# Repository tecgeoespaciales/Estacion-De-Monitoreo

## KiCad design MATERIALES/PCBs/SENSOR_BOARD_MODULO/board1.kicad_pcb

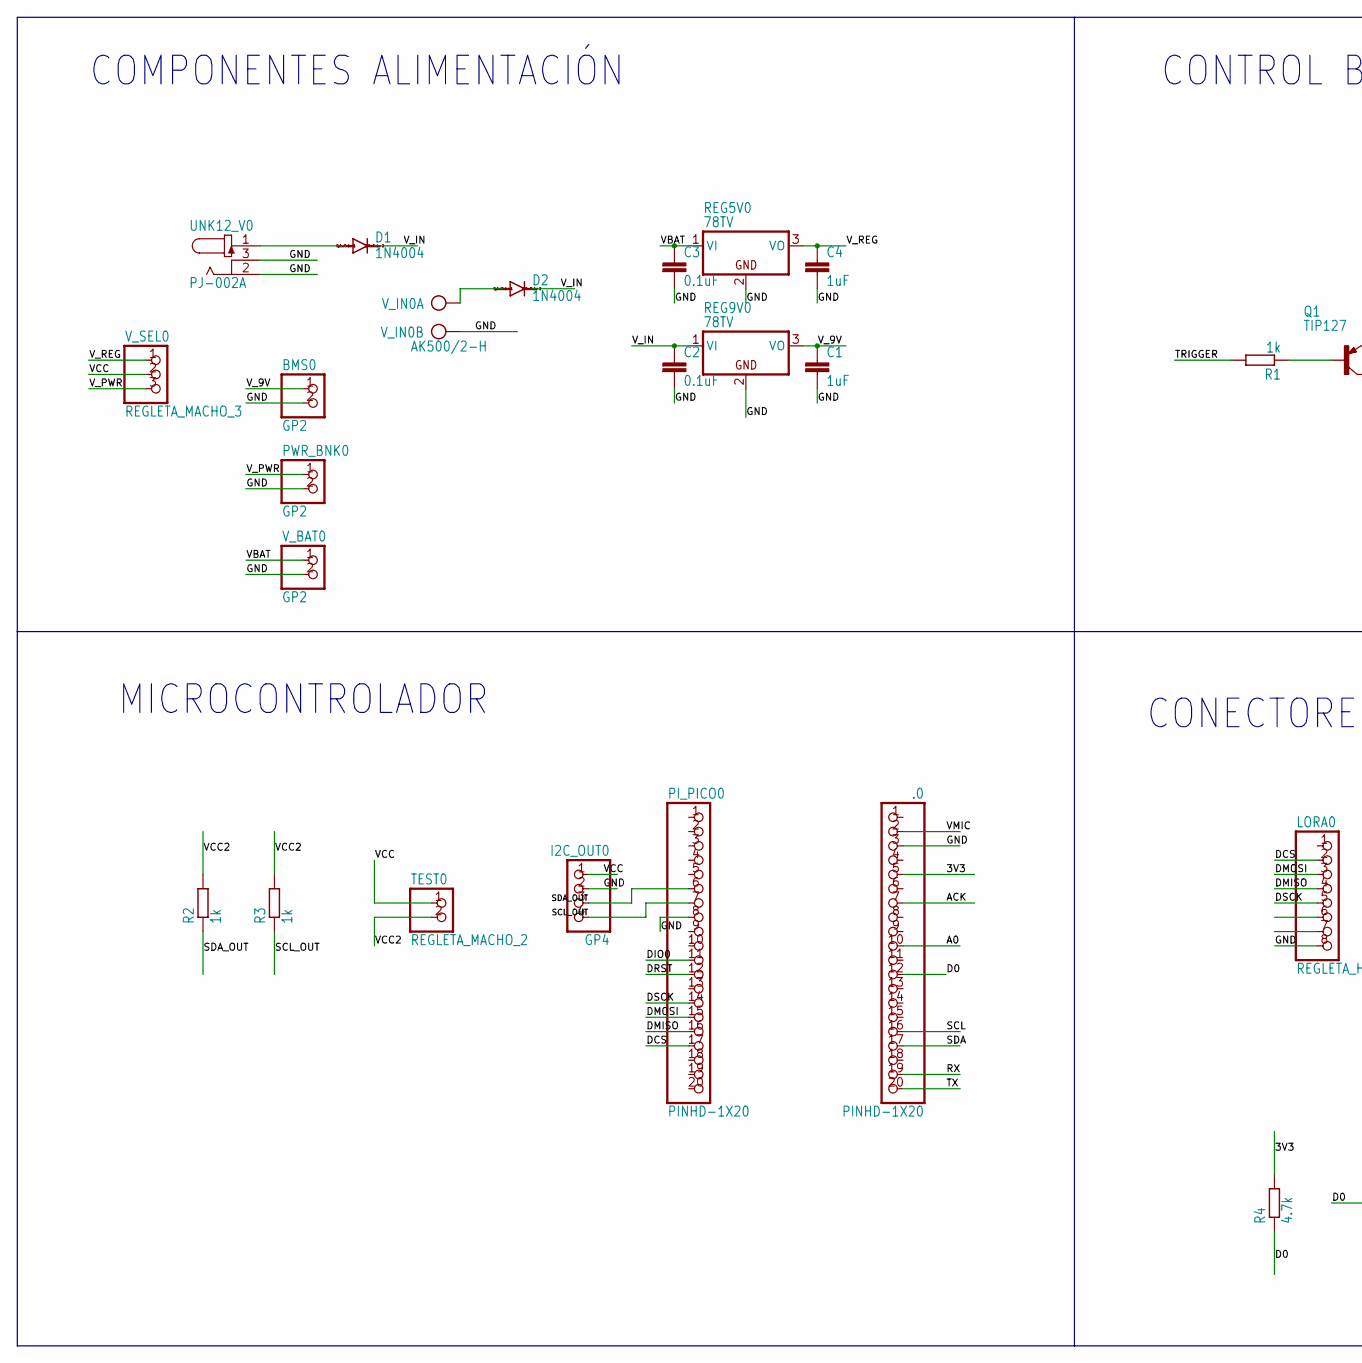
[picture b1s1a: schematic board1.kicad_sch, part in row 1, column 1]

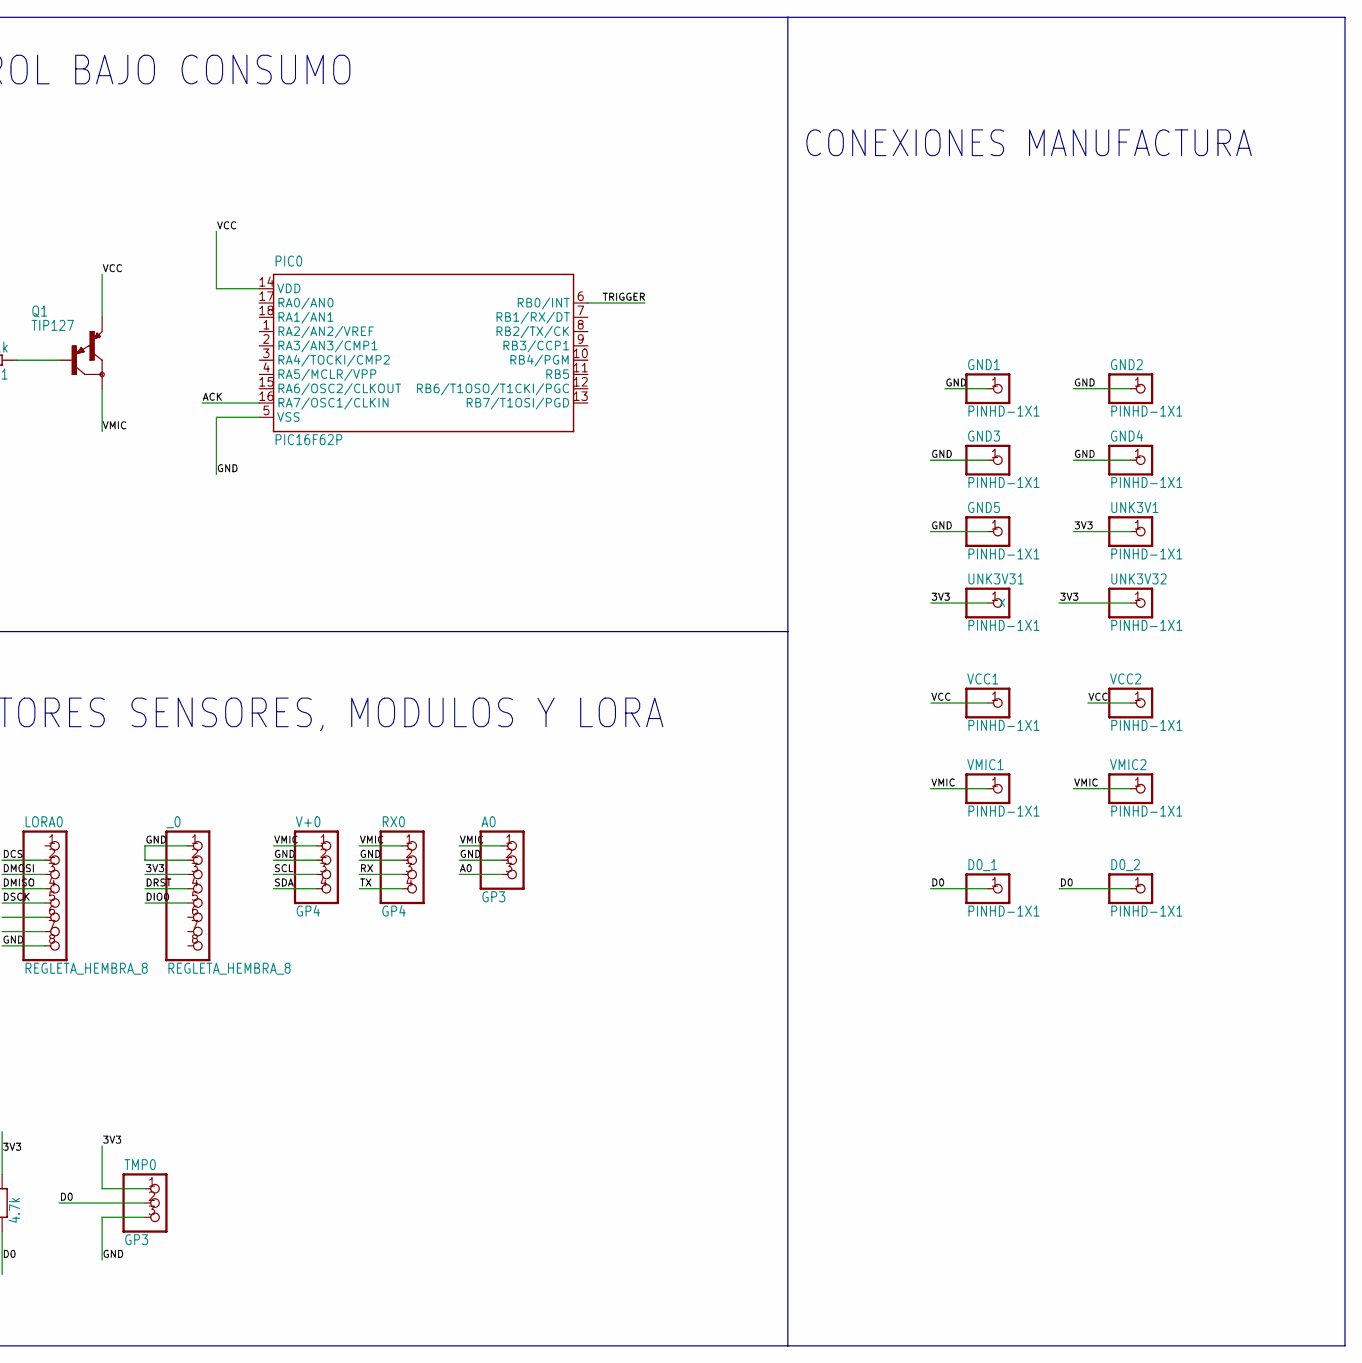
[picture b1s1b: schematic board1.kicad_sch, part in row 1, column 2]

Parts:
.0: PINHD-1X20; 1X20
A0: GP3; 1X03
BMS0: GP2; 1X02
C1, C4: 1uF; C025-024X044
C2, C3: 0.1uF; C025-024X044
D0_1, D0_2: PINHD-1X1; 1X01
D1, D2: 1N4004; DO41-10
GND1, GND2, GND3, GND4, GND5: PINHD-1X1; 1X01
I2C_OUT0: GP4; 1X04
LORA0: REGLETA_HEMBRA_8; 1X08
PIC0: PIC16F62P; DIL18
PI_PICO0: PINHD-1X20; 1X20
PWR_BNK0: GP2; 1X02
Q1: TIP127; TO220
R1, R2, R3: 1k; 0204_7
R4: 4.7k; 0204_7
REG5V0, REG9V0: 78TV; TO220V
RX0: GP4; 1X04
TEST0: REGLETA_MACHO_2; 1X02
TMP0: GP3; 1X03
UNK3V1, UNK3V31, UNK3V32: PINHD-1X1; 1X01
UNK12_V0: PJ-002A; CUI_PJ-002A
V+0: GP4; 1X04
VCC1, VCC2: PINHD-1X1; 1X01
VMIC1, VMIC2: PINHD-1X1; 1X01
V_BAT0: GP2; 1X02
V_IN0: AK500/2-H; AK500_2-H
V_SEL0: REGLETA_MACHO_3; 1X03
_0: REGLETA_HEMBRA_8; 1X08

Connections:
3V3: .0.5, R4.2, TMP0.1, UNK3V1.1, UNK3V31.1, UNK3V32.1, _0.3
A0: .0.10, A0.3
ACK: .0.7, PIC0.16 (RA7/OSC1/CLKIN)
D0: .0.12, D0_1.1, D0_2.1, R4.1, TMP0.2
DCS: LORA0.2, PI_PICO0.17
DIO0: PI_PICO0.11, _0.5
DMISO: LORA0.4, PI_PICO0.16
DMOSI: LORA0.3, PI_PICO0.15
DRST: PI_PICO0.12, _0.4
DSCK: LORA0.5, PI_PICO0.14
GND: .0.3, A0.2, BMS0.2, C1.2, C2.2, C3.2, C4.2, GND1.1, GND2.1, GND3.1, GND4.1, GND5.1, I2C_OUT0.2, LORA0.8, PIC0.5 (VSS), PI_PICO0.8, PWR_BNK0.2, REG5V0.2 (GND), REG9V0.2 (GND), RX0.2, TMP0.3, UNK12_V0.2, UNK12_V0.3, V+0.2, V_BAT0.2, V_IN0.2, _0.1, _0.2
unnamed: D1.A, UNK12_V0.1
unnamed: Q1.1 (B), R1.1
unnamed: D2.A, V_IN0.1
RX: .0.19, RX0.3
SCL: .0.16, V+0.3
SCL_OUT: I2C_OUT0.4, PI_PICO0.7, R3.1
SDA: .0.17, V+0.4
SDA_OUT: I2C_OUT0.3, PI_PICO0.6, R2.1
TRIGGER: PIC0.6 (RB0/INT), R1.2
TX: .0.20, RX0.4
VBAT: C3.1, REG5V0.1 (VI), V_BAT0.1
VCC: I2C_OUT0.1, PIC0.14 (VDD), Q1.3 (E), TEST0.1, VCC1.1, VCC2.1, V_SEL0.2
VCC2: R2.2, R3.2, TEST0.2
VMIC: .0.2, A0.1, Q1.2 (C), RX0.1, V+0.1, VMIC1.1, VMIC2.1
V_9V: BMS0.1, C1.1, REG9V0.3 (VO)
V_IN: C2.1, D1.C, D2.C, REG9V0.1 (VI)
V_PWR: PWR_BNK0.1, V_SEL0.3
V_REG: C4.1, REG5V0.3 (VO), V_SEL0.1

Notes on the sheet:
CONECTORES SENSORES, MODULOS Y LORA
CONEXIONES MANUFACTURA
CONTROL BAJO CONSUMO
MICROCONTROLADOR
COMPONENTES ALIMENTACIÓN

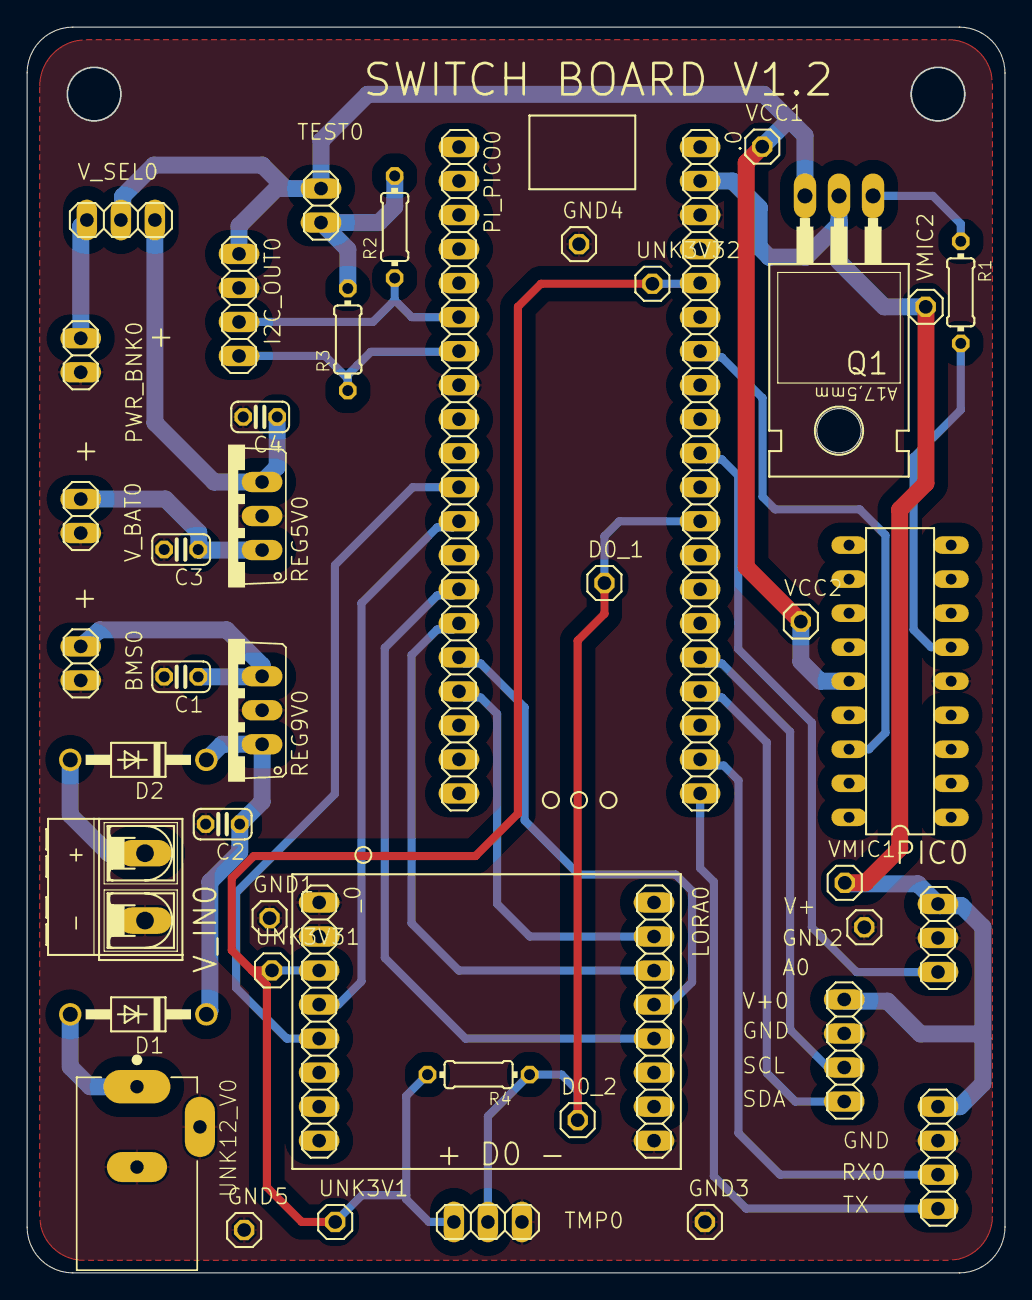
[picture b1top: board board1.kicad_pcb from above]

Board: 2 copper layers, 72.9 x 92.9 mm, 44 parts (0 on the bottom side), 29 nets.

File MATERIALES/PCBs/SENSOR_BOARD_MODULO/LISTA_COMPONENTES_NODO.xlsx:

Reference | Qty | Value | DNP | Exclude from BOM | Exclude from Board | Footprint | Datasheet
PI_PICO | 1 | PI_PICO |  |  |  | board1:PI_PICO
.0,PI_PICO0 | 2 | REGLETA_HEMBRA_20 |  |  |  | board1:1X20
A0,TMP0 | 2 | GP3 |  |  |  | board1:1X03
BMS0,PWR_BNK0,V_BAT0 | 3 | GP2 |  |  |  | board1:1X02
C1,C4 | 2 | 1uF |  |  |  | board1:C025-024X044
C2,C3 | 2 | 0.1uF |  |  |  | board1:C025-024X044
D0_1,D0_2,GND1,GND2,GND3,GND4,GND5,UNK3V1,UNK3V31,UNK3V32,VCC1,VCC2,VMIC1,VMIC2 | 14 | PINHD-1X1 |  |  |  | board1:1X01
D1,D2 | 2 | 1N4004 |  |  |  | board1:DO41-10
I2C_OUT0,RX0,V+0 | 3 | GP4 |  |  |  | board1:1X04
LORA0,_0 | 2 | REGLETA_HEMBRA_8 |  |  |  | board1:1X08
PIC0 | 1 | PIC16F62P |  |  |  | board1:DIL18
Q1 | 1 | TIP127 |  |  |  | board1:TO220
R1,R2,R3 | 3 | 1k |  |  |  | board1:0204_7
R4 | 1 | 4.7k |  |  |  | board1:0204_7
REG5V0,REG9V0 | 2 | 78TV |  |  |  | board1:TO220V
TEST0 | 1 | REGLETA_MACHO_2 |  |  |  | board1:1X02
UNK12_V0 | 1 | PJ-002A |  |  |  | board1:CUI_PJ-002A
V_IN0 | 1 | AK500/2-H |  |  |  | board1:AK500_2-H
V_SEL0 | 1 | REGLETA_MACHO_3 |  |  |  | board1:1X03

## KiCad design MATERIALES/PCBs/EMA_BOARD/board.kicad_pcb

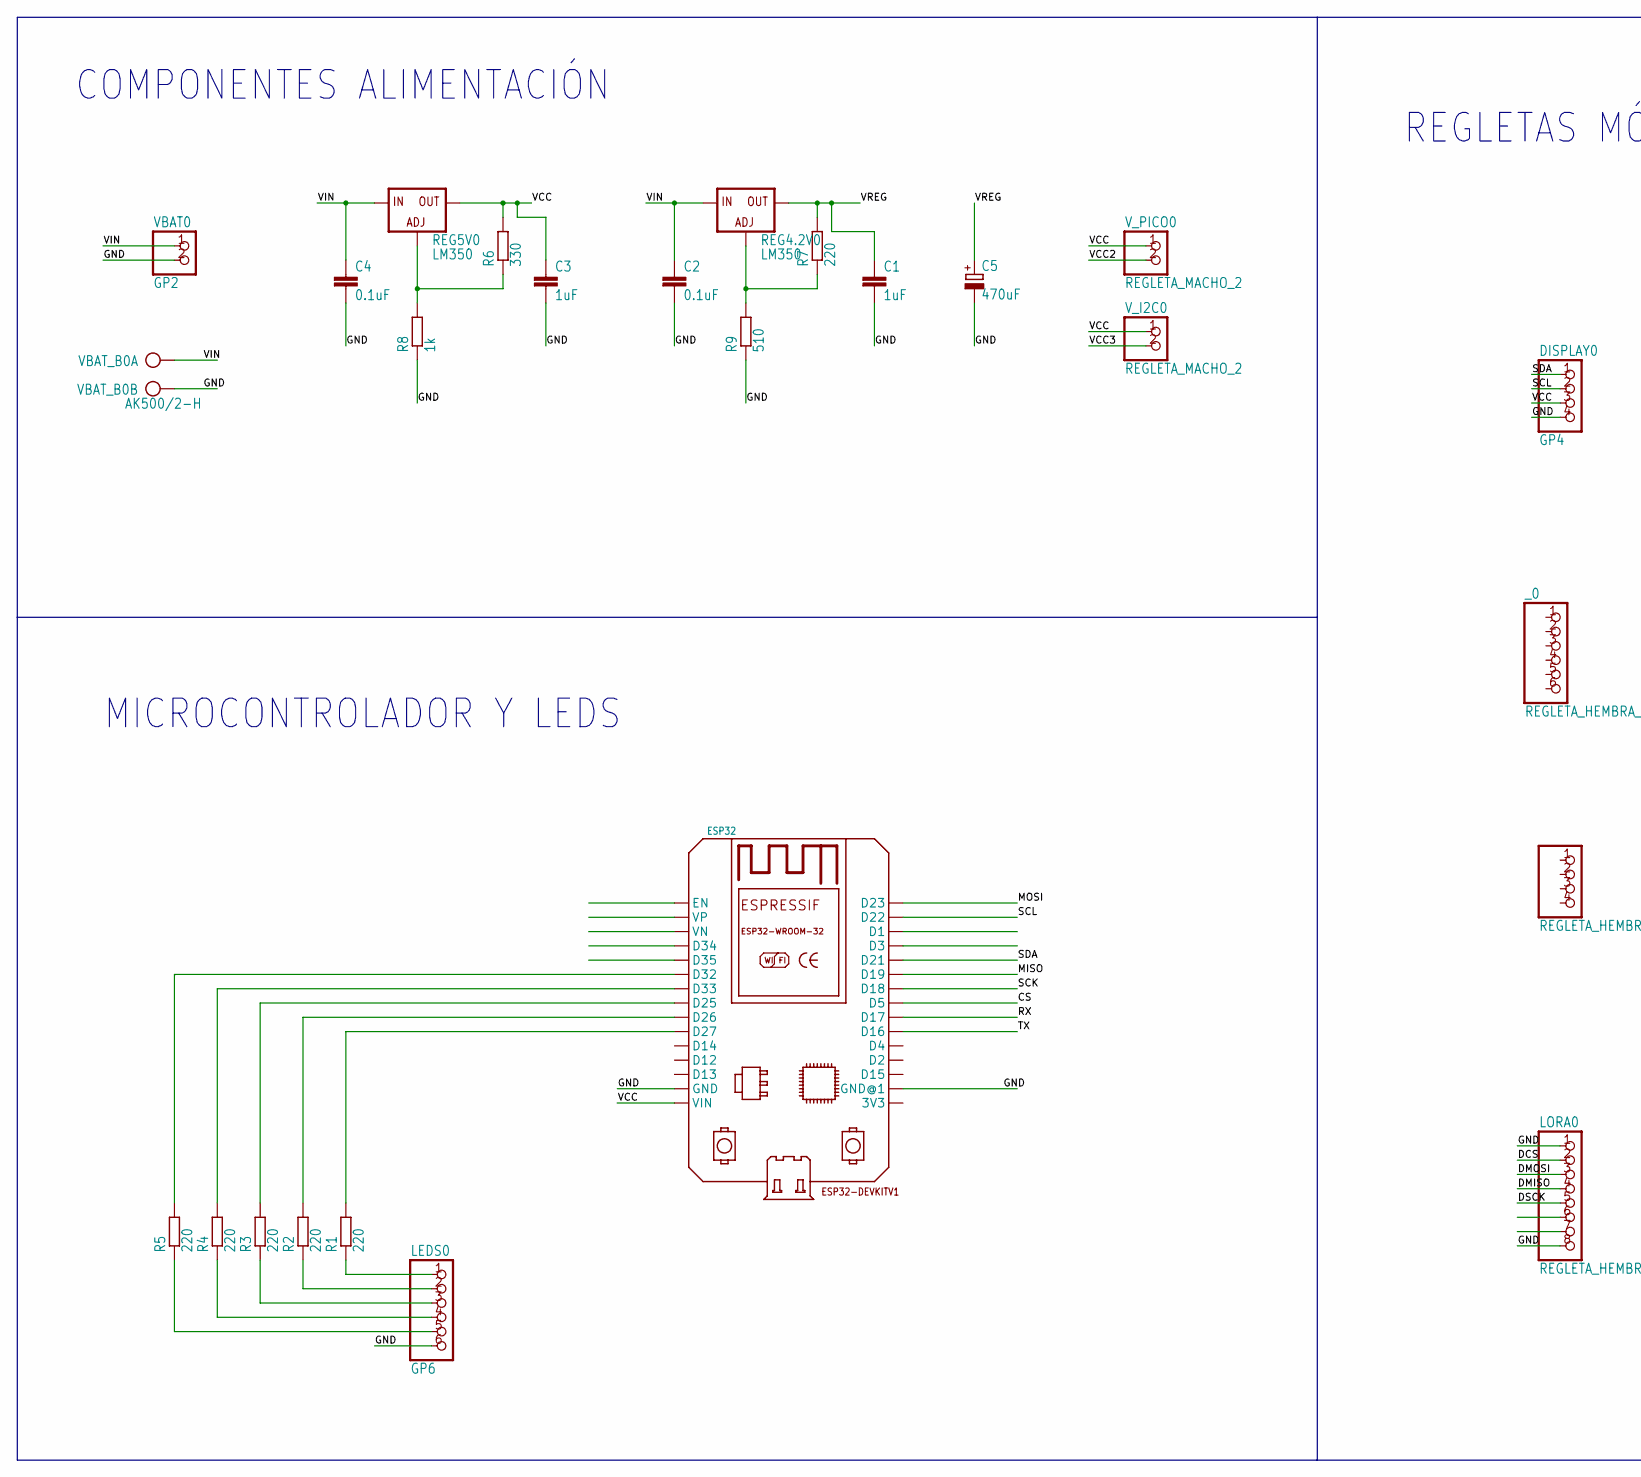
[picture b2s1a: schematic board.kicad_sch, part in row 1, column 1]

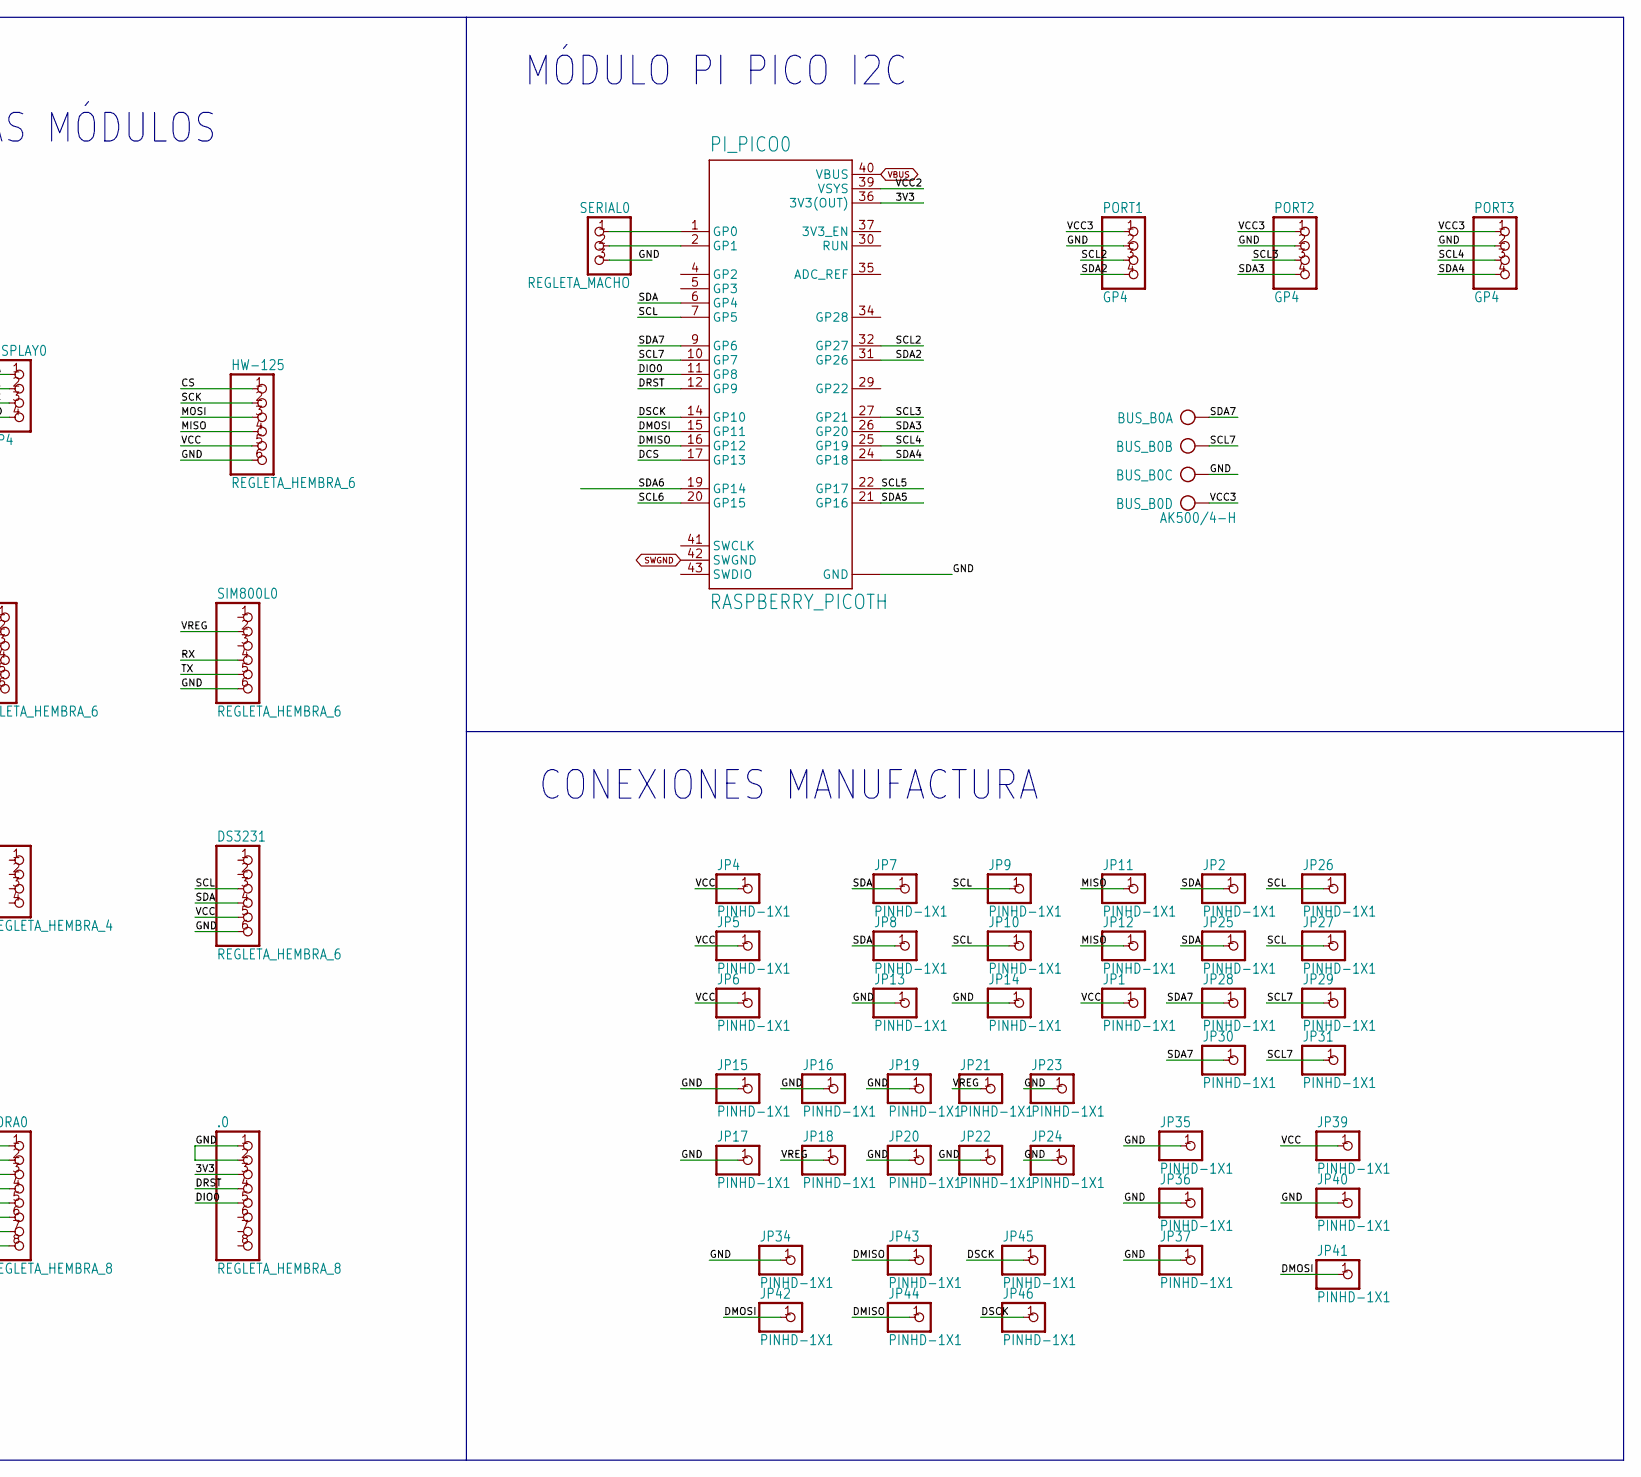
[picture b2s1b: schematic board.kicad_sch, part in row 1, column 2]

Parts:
.0: REGLETA_HEMBRA_8; 1X08
BUS_B0: AK500/4-H; AK500_4-H
C1, C3: 1uF; C2.5-2
C2, C4: 0.1uF; C2.5-2
C5: 470uF; E3,5-8
DISPLAY0: GP4; 1X04
DS3231: REGLETA_HEMBRA_6; 1X06
ESP32: ESP32DEVKITV1; ESP32-DEVKITV1
HW-125: REGLETA_HEMBRA_6; 1X06
JP1, JP2, JP4, JP5, JP6, JP7, JP8, JP9, JP10, JP11, JP12, JP13, JP14, JP15, JP16, JP17, JP18, JP19, JP20, JP21, JP22, JP23, JP24, JP25, JP26, JP27, JP28, JP29, JP30, JP31, JP34, JP35, JP36, JP37, JP39, JP40, JP41, JP42, JP43, JP44, JP45, JP46: PINHD-1X1; 1X01
LEDS0: GP6; 1X06
LORA0: REGLETA_HEMBRA_8; 1X08
PI_PICO0: RASPBERRY_PICOTH; PICO-PKG-TH
PORT1, PORT2, PORT3: GP4; 1X04
R1, R2, R3, R4, R5, R7: 220; 0204_7
R6: 330; 0204_7
R8: 1k; 0204_7
R9: 510; 0204_7
REG4.2V0, REG5V0: LM350; 317TS
SERIAL0: REGLETA_MACHO; 1X03
SIM800L0: REGLETA_HEMBRA_6; 1X06
VBAT0: GP2; 1X02
VBAT_B0: AK500/2-H; AK500_2-H
V_I2C0: REGLETA_MACHO_2; 1X02
V_PICO0: REGLETA_MACHO_2; 1X02
_: REGLETA_HEMBRA_4; 1X04
_0: REGLETA_HEMBRA_6; 1X06

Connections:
3V3: .0.3, PI_PICO0.36 (3V3(OUT))
CS: ESP32.D5, HW-125.1
DCS: LORA0.2, PI_PICO0.17 (GP13)
DIO0: .0.5, PI_PICO0.11 (GP8)
DMISO: JP43.1, JP44.1, LORA0.4, PI_PICO0.16 (GP12)
DMOSI: JP41.1, JP42.1, LORA0.3, PI_PICO0.15 (GP11)
DRST: .0.4, PI_PICO0.12 (GP9)
DSCK: JP45.1, JP46.1, LORA0.5, PI_PICO0.14 (GP10)
GND: .0.1, .0.2, BUS_B0.3, C1.2, C2.2, C3.2, C4.2, C5.-, DISPLAY0.4, DS3231.6, ESP32.GND, ESP32.GND@1, HW-125.6, JP13.1, JP14.1, JP15.1, JP16.1, JP17.1, JP19.1, JP20.1, JP22.1, JP23.1, JP24.1, JP34.1, JP35.1, JP36.1, JP37.1, JP40.1, LEDS0.6, LORA0.1, LORA0.8, PI_PICO0.3 (GND), PI_PICO0.8 (GND), PI_PICO0.13 (GND), PI_PICO0.18 (GND), PI_PICO0.23 (GND), PI_PICO0.28 (GND), PI_PICO0.33 (GND), PI_PICO0.38 (GND), PORT1.2, PORT2.2, PORT3.2, R8.1, R9.1, SERIAL0.3, SIM800L0.6, VBAT0.2, VBAT_B0.2
MISO: ESP32.D19, HW-125.4, JP11.1, JP12.1
MOSI: ESP32.D23, HW-125.3
unnamed: ESP32.D32, R5.2
unnamed: ESP32.D33, R4.2
unnamed: ESP32.D25, R3.2
unnamed: ESP32.D26, R2.2
unnamed: ESP32.D27, R1.2
unnamed: LEDS0.1, R1.1
unnamed: PI_PICO0.1 (GP0), SERIAL0.1
unnamed: LEDS0.2, R2.1
unnamed: LEDS0.3, R3.1
unnamed: LEDS0.4, R4.1
unnamed: LEDS0.5, R5.1
unnamed: PI_PICO0.2 (GP1), SERIAL0.2
unnamed: R6.1, R8.2, REG5V0.1 (ADJ)
unnamed: R7.1, R9.2, REG4.2V0.1 (ADJ)
RX: ESP32.D17, SIM800L0.4
SCK: ESP32.D18, HW-125.2
SCL: DISPLAY0.2, DS3231.3, ESP32.D22, JP9.1, JP10.1, JP26.1, JP27.1, PI_PICO0.7 (GP5)
SCL2: PI_PICO0.32 (GP27), PORT1.3
SCL3: PI_PICO0.27 (GP21), PORT2.3
SCL4: PI_PICO0.25 (GP19), PORT3.3
SCL5: PI_PICO0.22 (GP17)
SCL6: PI_PICO0.20 (GP15)
SCL7: BUS_B0.2, JP29.1, JP31.1, PI_PICO0.10 (GP7)
SDA: DISPLAY0.1, DS3231.4, ESP32.D21, JP2.1, JP7.1, JP8.1, JP25.1, PI_PICO0.6 (GP4)
SDA2: PI_PICO0.31 (GP26), PORT1.4
SDA3: PI_PICO0.26 (GP20), PORT2.4
SDA4: PI_PICO0.24 (GP18), PORT3.4
SDA5: PI_PICO0.21 (GP16)
SDA6: PI_PICO0.19 (GP14)
SDA7: BUS_B0.1, JP28.1, JP30.1, PI_PICO0.9 (GP6)
SWGND: PI_PICO0.42 (SWGND)
TX: ESP32.D16, SIM800L0.5
VBUS: PI_PICO0.40 (VBUS)
VCC: C3.1, DISPLAY0.3, DS3231.5, ESP32.VIN, HW-125.5, JP1.1, JP4.1, JP5.1, JP6.1, JP39.1, R6.2, REG5V0.2 (OUT), V_I2C0.1, V_PICO0.1
VCC2: PI_PICO0.39 (VSYS), V_PICO0.2
VCC3: BUS_B0.4, PORT1.1, PORT2.1, PORT3.1, V_I2C0.2
VIN: C2.1, C4.1, REG4.2V0.3 (IN), REG5V0.3 (IN), VBAT0.1, VBAT_B0.1
VREG: C1.1, C5.+, JP18.1, JP21.1, R7.2, REG4.2V0.2 (OUT), SIM800L0.2

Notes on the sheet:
REGLETAS MÓDULOS
MÓDULO PI PICO I2C
COMPONENTES ALIMENTACIÓN
MICROCONTROLADOR Y LEDS
CONEXIONES MANUFACTURA

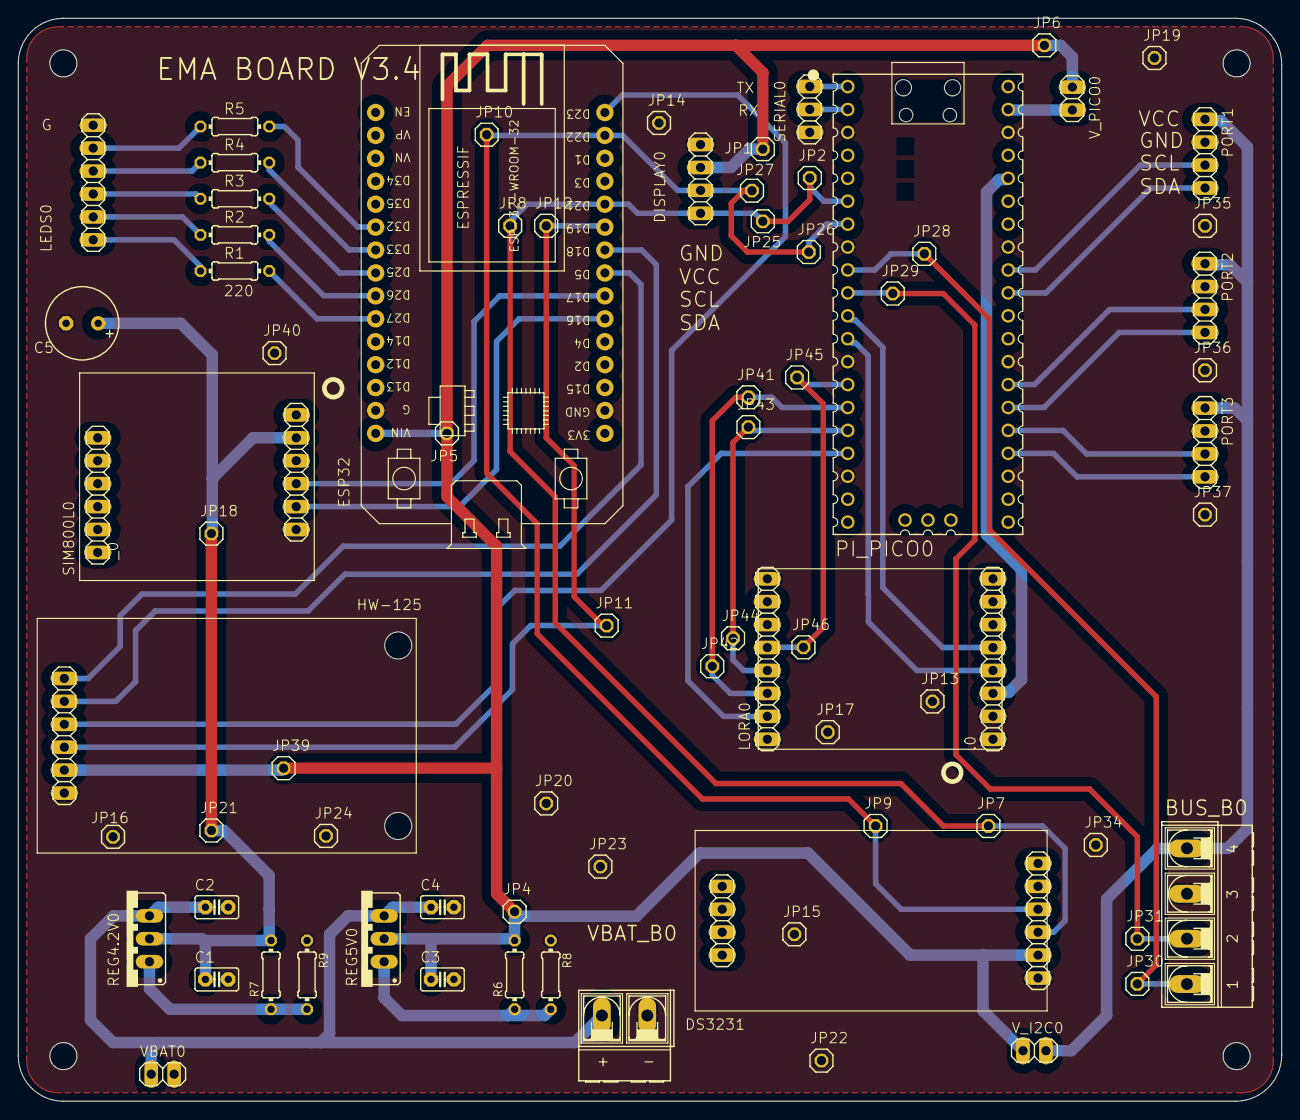
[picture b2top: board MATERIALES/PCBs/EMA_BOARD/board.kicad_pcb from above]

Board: 2 copper layers, 139.9 x 119.9 mm, 78 parts (0 on the bottom side), 43 nets.

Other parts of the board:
JP3: 1X04_325

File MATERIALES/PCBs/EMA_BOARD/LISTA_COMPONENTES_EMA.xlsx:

Reference | Qty | Value | DNP | Exclude from BOM | Exclude from Board | Footprint | Datasheet
.0,LORA0 | 2 | REGLETA_HEMBRA_8 |  |  |  | board:1X08
BUS_B0 | 1 | AK500/4-H |  |  |  | board:AK500_4-H
C1,C3 | 2 | 1uF |  |  |  | board:C2.5-2
C2,C4 | 2 | 0.1uF |  |  |  | board:C2.5-2
C5 | 1 | 470uF |  |  |  | board:E3,5-8
DISPLAY0,PORT1,PORT2,PORT3 | 4 | GP4 |  |  |  | board:1X04
DS3231,HW-125,SIM800L0,_0 | 4 | REGLETA_HEMBRA_6 |  |  |  | board:1X06
ESP32 | 1 | ESP32DEVKITV1 |  |  |  | board:ESP32-DEVKITV1
ESP32_1,ESP32_2 | 2 | REGLETA_HEMBRA_15 |  |  |  | board:1x15
JP1,JP2,JP4,JP5,JP6,JP7,JP8,JP9,JP10,JP11,JP12,JP13,JP14,JP15,JP16,JP17,JP18,JP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 | 42 | PINHD-1X1 |  |  |  | board:1X01
LEDS0 | 1 | GP6 |  |  |  | board:1X06
PI_PICO0 | 1 | RASPBERRY_PICOTH |  |  |  | board:PICO-PKG-TH
PI_PICO0_1,PI_PICO0_2 | 2 | REGLETA_HEMBRA_20 |  |  |  | board:1x20
R1,R2,R3,R4,R5,R7 | 6 | 220 |  |  |  | board:0204_7
R6 | 1 | 330 |  |  |  | board:0204_7
R8 | 1 | 1k |  |  |  | board:0204_7
R9 | 1 | 510 |  |  |  | board:0204_7
REG4.2V0,REG5V0 | 2 | LM350 |  |  |  | board:317TS
SERIAL0 | 1 | REGLETA_MACHO |  |  |  | board:1X03
VBAT0 | 1 | GP2 |  |  |  | board:1X02
VBAT_B0 | 1 | AK500/2-H |  |  |  | board:AK500_2-H
V_I2C0,V_PICO0 | 2 | REGLETA_MACHO_2 |  |  |  | board:1X02
_? | 1 | REGLETA_HEMBRA_4 |  |  |  | board:1X04

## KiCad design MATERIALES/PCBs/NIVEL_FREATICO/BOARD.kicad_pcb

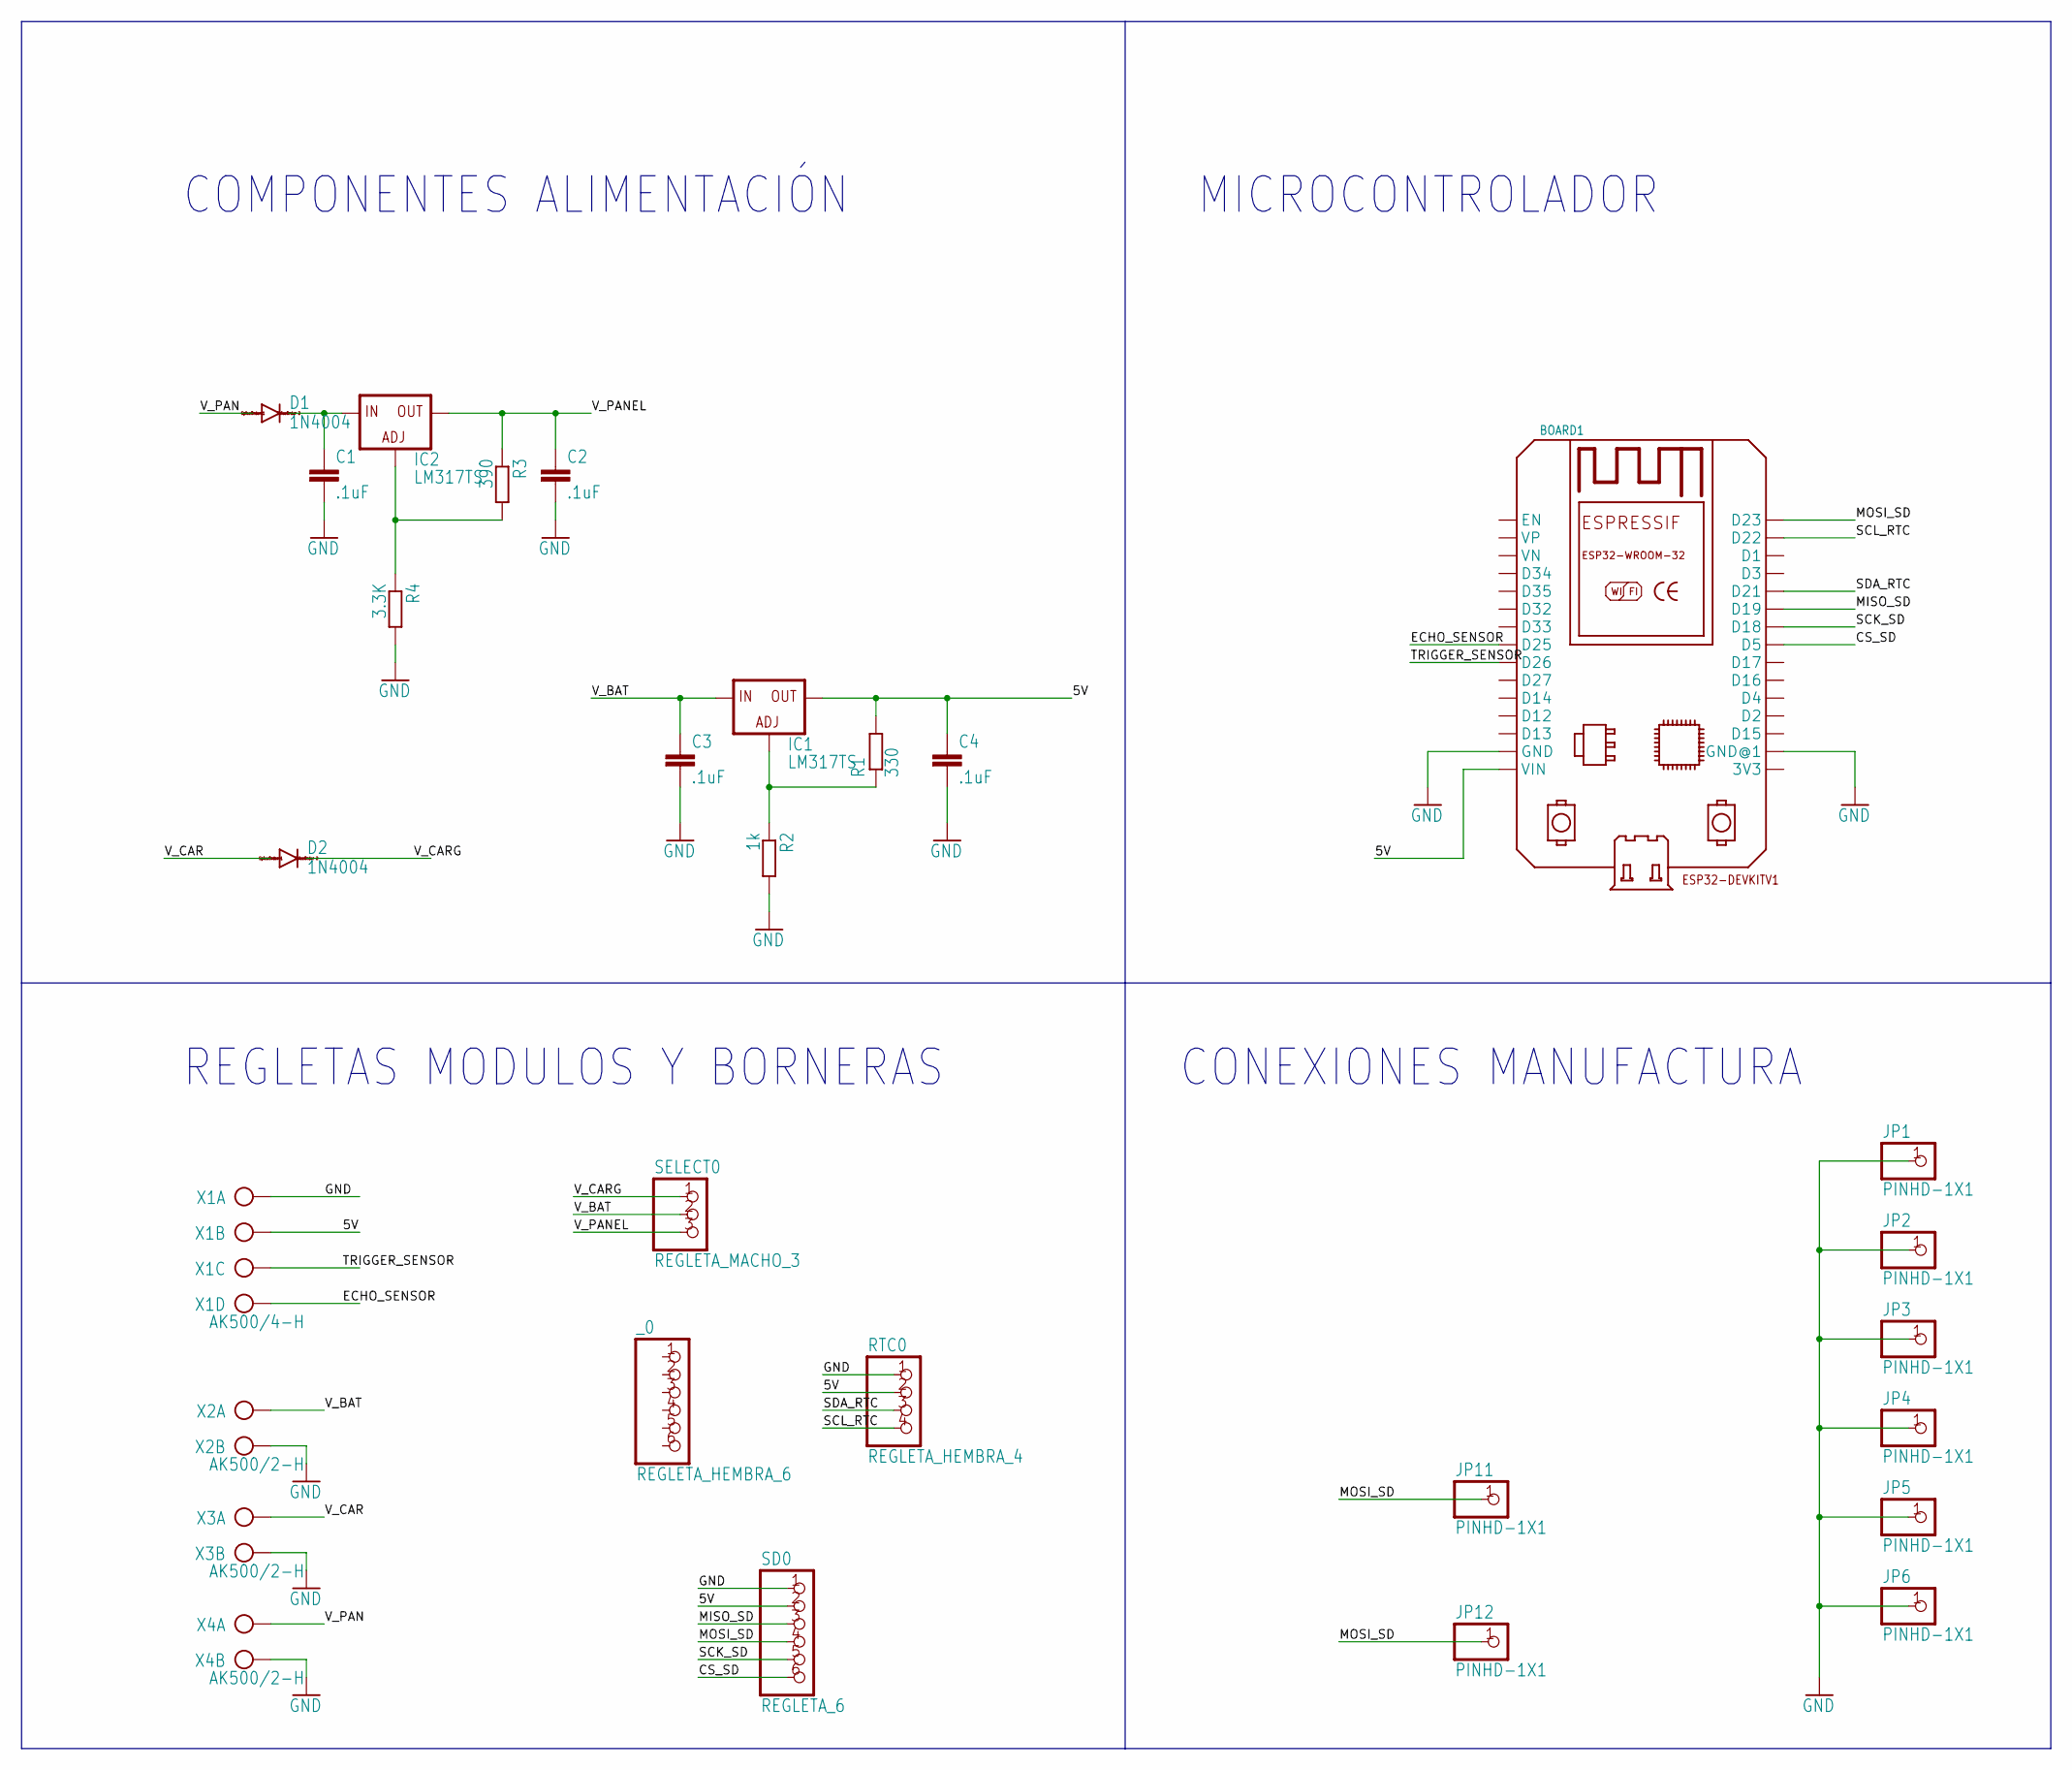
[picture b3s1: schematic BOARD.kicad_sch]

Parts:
BOARD1: ESP32DEVKITV1; ESP32-DEVKITV1
C1, C2, C3, C4: .1uF; C5B2.5
D1, D2: 1N4004; D-7.5
IC1, IC2: LM317TS; 317TS
JP1, JP2, JP3, JP4, JP5, JP6, JP11, JP12: PINHD-1X1; 1X01
R1: 330; 0204_7
R2: 1k; 0204_7
R3: 390; 0204_7
R4: 3.3K; 0204_7
RTC0: REGLETA_HEMBRA_4; 1X04
SD0: REGLETA_6; 1X06
SELECT0: REGLETA_MACHO_3; 1X03
X1: AK500/4-H; AK500_4-H
X2, X3, X4: AK500/2-H; AK500_2-H
_0: REGLETA_HEMBRA_6; 1X06

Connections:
5V: BOARD1.VIN, C4.1, IC1.2 (OUT), R1.2, RTC0.2, SD0.2, X1.2
CS_SD: BOARD1.D5, SD0.6
ECHO_SENSOR: BOARD1.D25, X1.4
GND: BOARD1.GND, BOARD1.GND@1, C1.2, C2.2, C3.2, C4.2, JP1.1, JP2.1, JP3.1, JP4.1, JP5.1, JP6.1, R2.2, R4.2, RTC0.1, SD0.1, X1.1, X2.2, X3.2, X4.2
MISO_SD: BOARD1.D19, SD0.3
MOSI_SD: BOARD1.D23, JP11.1, JP12.1, SD0.4
unnamed: IC2.1 (ADJ), R3.2, R4.1
unnamed: IC1.1 (ADJ), R1.1, R2.1
unnamed: C1.1, D1.C, IC2.3 (IN)
SCK_SD: BOARD1.D18, SD0.5
SCL_RTC: BOARD1.D22, RTC0.4
SDA_RTC: BOARD1.D21, RTC0.3
TRIGGER_SENSOR: BOARD1.D26, X1.3
V_BAT: C3.1, IC1.3 (IN), SELECT0.2, X2.1
V_CAR: D2.A, X3.1
V_CARG: D2.C, SELECT0.1
V_PAN: D1.A, X4.1
V_PANEL: C2.1, IC2.2 (OUT), R3.1, SELECT0.3

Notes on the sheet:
CONEXIONES MANUFACTURA
MICROCONTROLADOR
COMPONENTES ALIMENTACIÓN
REGLETAS MODULOS Y BORNERAS

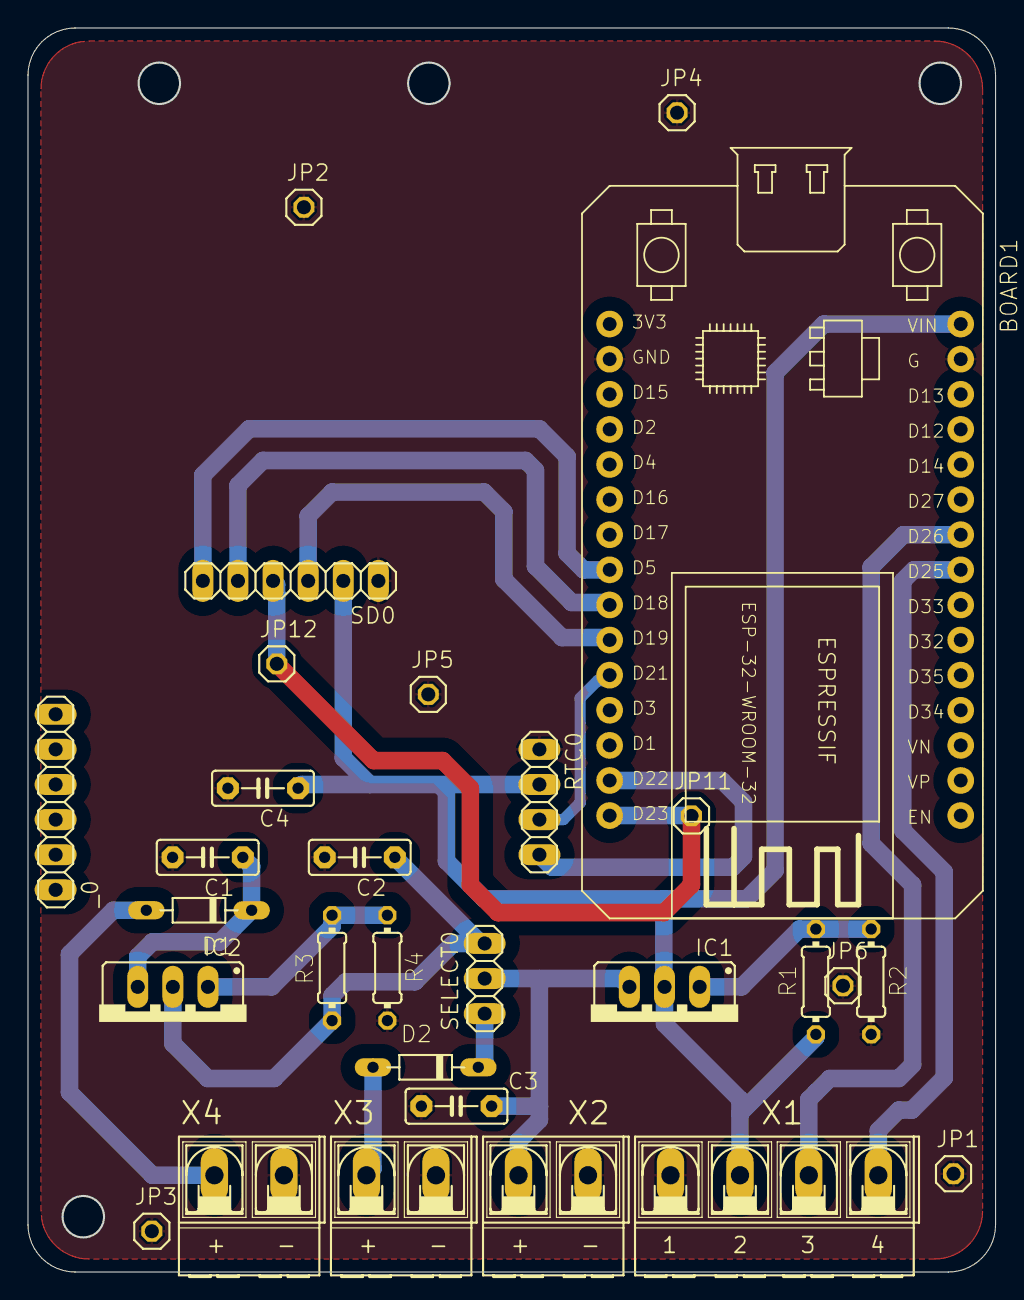
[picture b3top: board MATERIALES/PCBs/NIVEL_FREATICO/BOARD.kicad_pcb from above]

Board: 2 copper layers, 69.9 x 89.9 mm, 29 parts (0 on the bottom side), 18 nets.

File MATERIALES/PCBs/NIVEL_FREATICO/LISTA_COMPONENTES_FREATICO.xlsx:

Reference | Qty | Value | DNP | Exclude from BOM | Exclude from Board | Footprint | Datasheet
BOARD1 | 1 | ESP32DEVKITV1 |  |  |  | BOARD:ESP32-DEVKITV1
BOARD1_1,BOARD1_2 | 2 | REGLETA_HEMBRA_15 |  |  |  | BOARD:1X15
C1,C2,C3,C4 | 4 | .1uF |  |  |  | BOARD:C5B2.5
D1,D2 | 2 | 1N4004 |  |  |  | BOARD:D-7.5
IC1,IC2 | 2 | LM317TS |  |  |  | BOARD:317TS
JP1,JP2,JP3,JP4,JP5,JP6,JP11,JP12 | 8 | PINHD-1X1 |  |  |  | BOARD:1X01
R1 | 1 | 330 |  |  |  | BOARD:0204_7
R2 | 1 | 1k |  |  |  | BOARD:0204_7
R3 | 1 | 390 |  |  |  | BOARD:0204_7
R4 | 1 | 3.3K |  |  |  | BOARD:0204_7
RTC0 | 1 | REGLETA_HEMBRA_4 |  |  |  | BOARD:1X04
SD0 | 1 | REGLETA_6 |  |  |  | BOARD:1X06
SELECT0 | 1 | REGLETA_MACHO_3 |  |  |  | BOARD:1X03
X1 | 1 | AK500/4-H |  |  |  | BOARD:AK500_4-H
X2,X3,X4 | 3 | AK500/2-H |  |  |  | BOARD:AK500_2-H
_0 | 1 | REGLETA_HEMBRA_6 |  |  |  | BOARD:1X06

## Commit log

2025-07-03 Primera Reestructuración
    Primera Reestructuración
2025-07-03 Update README.md
    Actualización README
2025-07-03 Commit inicial - estructura completa del proyecto
2025-07-03 borrar basura
2025-07-04 Update .gitignore
    se agrega .env
2025-07-04 cambio de prueba
    cambio de prueba
2025-07-04 Delete .env
    delete ,env
2025-07-04 copia codigo EMA
    Se sube una copia del código principal de EMA
2025-07-04 cambio de nombre a carpeta
2025-07-04 Create app-debug.apk
    apk de EMA para android
2025-07-04 Create tutoriales EMA.pdf
    Se agrega PDF,
    tutoriales de EMA.
    descripción y links de video
